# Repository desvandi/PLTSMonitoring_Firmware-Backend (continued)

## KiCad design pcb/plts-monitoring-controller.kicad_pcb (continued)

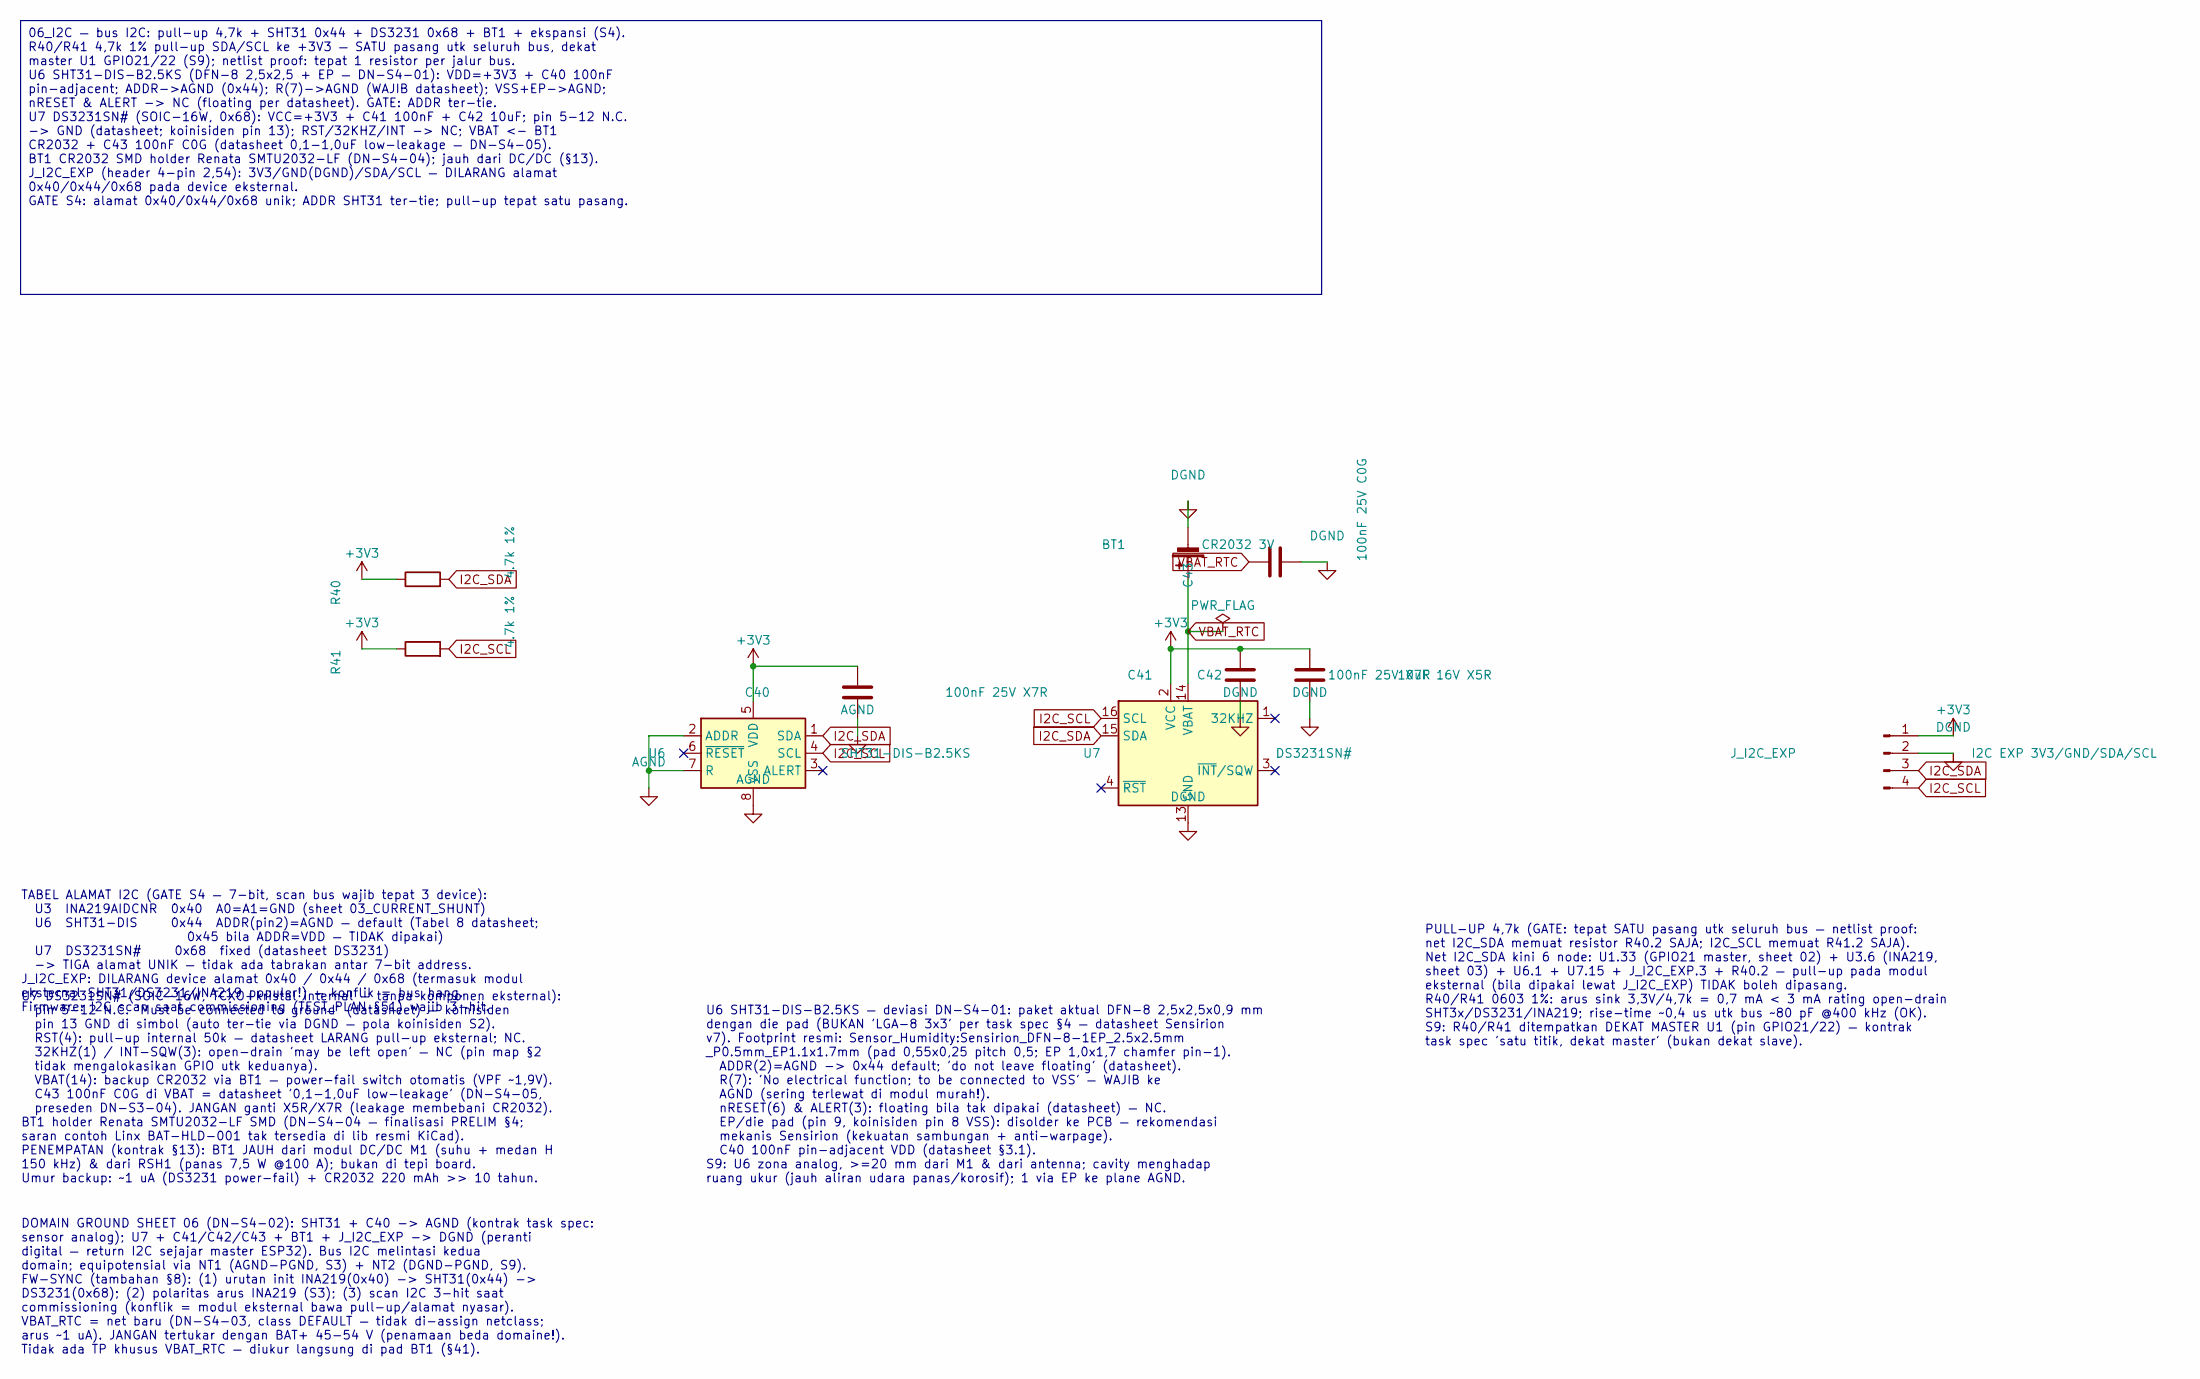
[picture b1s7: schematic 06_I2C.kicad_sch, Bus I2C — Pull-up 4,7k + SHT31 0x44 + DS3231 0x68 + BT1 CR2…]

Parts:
BT1: CR2032 3V; BatteryHolder_Renata_SMTU2032-LF_1x2032
C40, C41: 100nF 25V X7R; C_0603_1608Metric
C42: 10uF 16V X5R; C_0805_2012Metric
C43: 100nF 25V C0G; C_0603_1608Metric
J_I2C_EXP: I2C EXP 3V3/GND/SDA/SCL; PinHeader_1x04_P2.54mm_Vertical
R40, R41: 4.7k 1%; R_0603_1608Metric
U6: SHT31-DIS-B2.5KS; Sensirion_DFN-8-1EP_2.5x2.5mm_P0.5mm_EP1.1x1.7mm
U7: DS3231SN#; SOIC-16W_7.5x10.3mm_P1.27mm

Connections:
+3V3: C40.1, C41.1, C42.1, J_I2C_EXP.1, R40.1, R41.1, U6.5 (VDD), U7.2 (VCC); also elsewhere on the board
AGND: C40.2, U6.2 (ADDR), U6.7 (R), U6.8 (VSS), U6.9 (VSS); also elsewhere on the board
DGND: BT1.2 (-), C41.2, C42.2, C43.2, J_I2C_EXP.2, U7.5 (GND), U7.6 (GND), U7.7 (GND), U7.8 (GND), U7.9 (GND), U7.10 (GND), U7.11 (GND), U7.12 (GND), U7.13 (GND); also elsewhere on the board
I2C_SCL: J_I2C_EXP.4, R41.2, U6.4 (SCL), U7.16 (SCL); also elsewhere on the board
I2C_SDA: J_I2C_EXP.3, R40.2, U6.1 (SDA), U7.15 (SDA); also elsewhere on the board
VBAT_RTC: BT1.1 (+), C43.1, U7.14 (VBAT)

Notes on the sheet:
TABEL ALAMAT I2C (GATE S4 — 7-bit, scan bus wajib tepat 3 device): U3 INA219AIDCNR 0x40 A0=A1=GND (sheet 03_CURRENT_SHUNT) U6 SHT31-DIS 0x44 ADDR(pin2)=AGND — default (Tabel 8 datasheet; 0x45 bila ADDR=VDD — TIDAK dipakai) U7 DS3231SN# 0x68 fixed (datasheet DS3231) -> TIGA alamat UNIK — tidak ada t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
PULL-UP 4,7k (GATE: tepat SATU pasang utk seluruh bus — netlist proof: net I2C_SDA memuat resistor R40.2 SAJA; I2C_SCL memuat R41.2 SAJA). Net I2C_SDA kini 6 node: U1.33 (GPIO21 master, sheet 02) + U3.6 (INA219, sheet 03) + U6.1 + U7.15 + J_I2C_EXP.3 + R40.2 — pull-up pada modul eksternal (bila dip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
U7 DS3231SN# (SOIC-16W, TCXO+kristal internal — tanpa komponen eksternal): pin 5-12 N.C. 'Must be connected to ground' (datasheet) — koinisiden pin 13 GND di simbol (auto ter-tie via DGND — pola koinisiden S2). RST(4): pull-up internal 50k — datasheet LARANG pull-up eksternal; NC. 32KHZ(1) / INT-SQ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
U6 SHT31-DIS-B2.5KS — deviasi DN-S4-01: paket aktual DFN-8 2,5x2,5x0,9 mm dengan die pad (BUKAN 'LGA-8 3x3' per task spec §4 — datasheet Sensirion v7). Footprint resmi: Sensor_Humidity:Sensirion_DFN-8-1EP_2.5x2.5mm _P0.5mm_EP1.1x1.7mm (pad 0,55x0,25 pitch 0,5; EP 1,0x1,7 chamfer pin-1). ADDR(2)=AGN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
DOMAIN GROUND SHEET 06 (DN-S4-02): SHT31 + C40 -> AGND (kontrak task spec: sensor analog); U7 + C41/C42/C43 + BT1 + J_I2C_EXP -> DGND (peranti digital — return I2C sejajar master ESP32). Bus I2C melintasi kedua domain; equipotensial via NT1 (AGND-PGND, S3) + NT2 (DGND-PGND, S9). FW-SYNC (tambahan §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
06_I2C — bus I2C: pull-up 4,7k + SHT31 0x44 + DS3231 0x68 + BT1 + ekspansi (S4). R40/R41 4,7k 1% pull-up SDA/SCL ke +3V3 — SATU pasang utk seluruh bus, dekat master U1 GPIO21/22 (S9); netlist proof: tepat 1 resistor per jalur bus. U6 SHT31-DIS-B2.5KS (DFN-8 2,5x2,5 + EP — DN-S4-01): VDD=+3V3 + C40 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

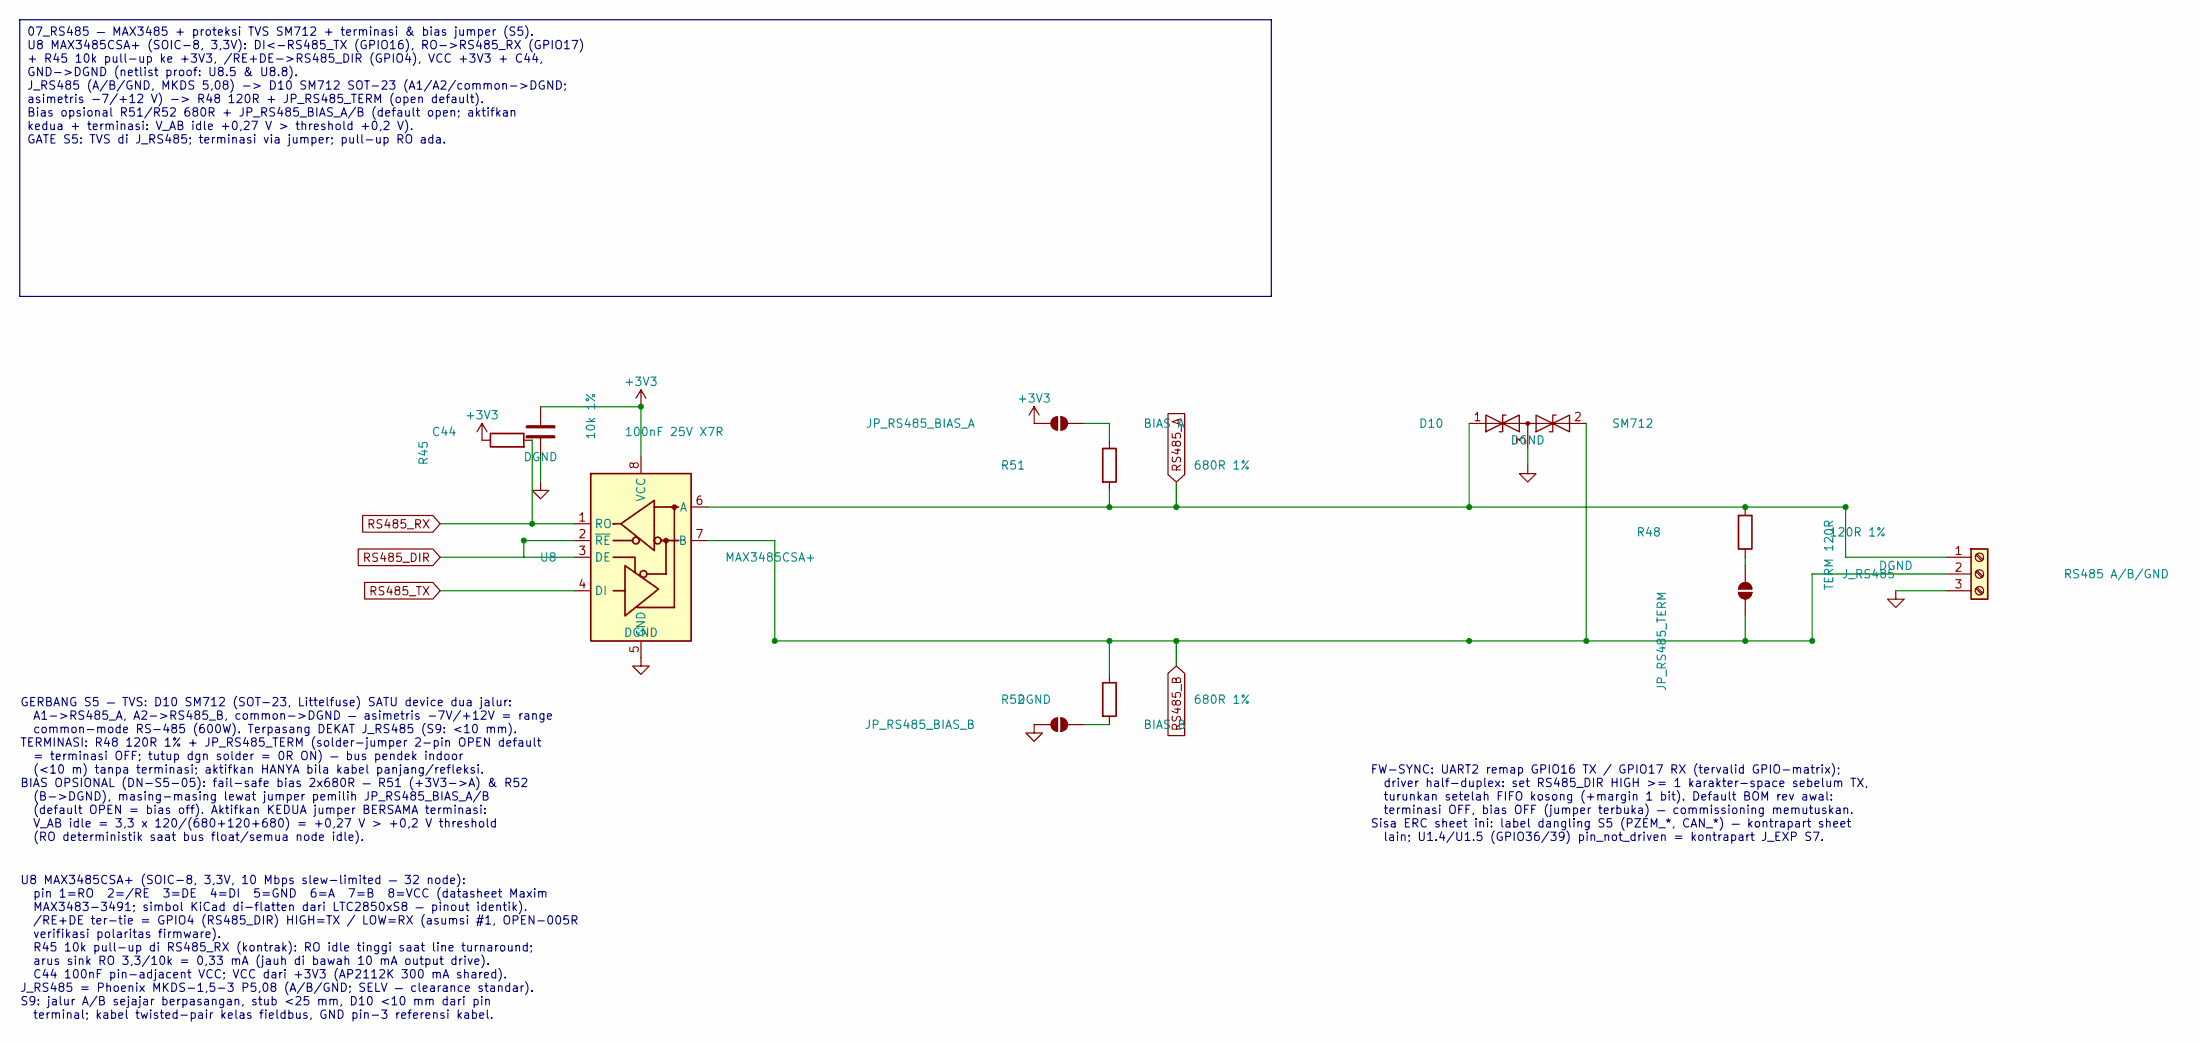
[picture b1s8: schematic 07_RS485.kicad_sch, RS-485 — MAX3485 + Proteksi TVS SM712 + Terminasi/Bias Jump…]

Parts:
C44: 100nF 25V X7R; C_0603_1608Metric
D10: SM712; SOT-23
JP_RS485_BIAS_A: BIAS A; SolderJumper-2_P1.3mm_Open_Pad1.0x1.5mm
JP_RS485_BIAS_B: BIAS B; SolderJumper-2_P1.3mm_Open_Pad1.0x1.5mm
JP_RS485_TERM: TERM 120R; SolderJumper-2_P1.3mm_Open_Pad1.0x1.5mm
J_RS485: RS485 A/B/GND; TerminalBlock_Phoenix_MKDS-1,5-3-5.08_1x03_P5.08mm_Horizont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
R45: 10k 1%; R_0603_1608Metric
R48: 120R 1%; R_0603_1608Metric
R51, R52: 680R 1%; R_0603_1608Metric
U8: MAX3485CSA+; SOIC-8_3.9x4.9mm_P1.27mm

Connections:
+3V3: C44.1, JP_RS485_BIAS_A.1 (A), R45.1, U8.8 (VCC); also elsewhere on the board
DGND: C44.2, D10.3 (common), JP_RS485_BIAS_B.1 (A), J_RS485.3, U8.5 (GND); also elsewhere on the board
unnamed: JP_RS485_BIAS_A.2 (B), R51.1
unnamed: JP_RS485_BIAS_B.2 (B), R52.2
unnamed: JP_RS485_TERM.2 (B), R48.2
RS485_A: D10.1 (A1), J_RS485.1, R48.1, R51.2, U8.6 (A); also elsewhere on the board
RS485_B: D10.2 (A2), JP_RS485_TERM.1 (A), J_RS485.2, R52.1, U8.7 (B); also elsewhere on the board
RS485_DIR: U8.2 (~RE), U8.3 (DE); also elsewhere on the board
RS485_RX: R45.2, U8.1 (RO); also elsewhere on the board
RS485_TX: U8.4 (DI); also elsewhere on the board

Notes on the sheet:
GERBANG S5 — TVS: D10 SM712 (SOT-23, Littelfuse) SATU device dua jalur: A1->RS485_A, A2->RS485_B, common->DGND — asimetris -7V/+12V = range common-mode RS-485 (600W). Terpasang DEKAT J_RS485 (S9: <10 mm). TERMINASI: R48 120R 1% + JP_RS485_TERM (solder-jumper 2-pin OPEN default = terminasi OFF; tutu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
U8 MAX3485CSA+ (SOIC-8, 3,3V, 10 Mbps slew-limited — 32 node): pin 1=RO 2=/RE 3=DE 4=DI 5=GND 6=A 7=B 8=VCC (datasheet Maxim MAX3483-3491; simbol KiCad di-flatten dari LTC2850xS8 — pinout identik). /RE+DE ter-tie = GPIO4 (RS485_DIR) HIGH=TX / LOW=RX (asumsi #1, OPEN-005R verifikasi polaritas firmwa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
FW-SYNC: UART2 remap GPIO16 TX / GPIO17 RX (tervalid GPIO-matrix); driver half-duplex: set RS485_DIR HIGH >= 1 karakter-space sebelum TX, turunkan setelah FIFO kosong (+margin 1 bit). Default BOM rev awal: terminasi OFF, bias OFF (jumper terbuka) — commissioning memutuskan. Sisa ERC sheet ini: labe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
07_RS485 — MAX3485 + proteksi TVS SM712 + terminasi & bias jumper (S5). U8 MAX3485CSA+ (SOIC-8, 3,3V): DI<-RS485_TX (GPIO16), RO->RS485_RX (GPIO17) + R45 10k pull-up ke +3V3, /RE+DE->RS485_DIR (GPIO4), VCC +3V3 + C44, GND->DGND (netlist proof: U8.5 & U8.8). J_RS485 (A/B/GND, MKDS 5,08) -> D10 SM712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

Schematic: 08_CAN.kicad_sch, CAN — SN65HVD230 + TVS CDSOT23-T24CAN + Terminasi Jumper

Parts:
C70: 100nF 25V X7R; C_0603_1608Metric
D20: CDSOT23-T24CAN; SOT-23
JP_CAN_TERM: TERM 120R; SolderJumper-2_P1.3mm_Open_Pad1.0x1.5mm
J_CAN: CAN CANH/CANL/GND; TerminalBlock_Phoenix_MKDS-1,5-3-5.08_1x03_P5.08mm_Horizont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
R49: 120R 1%; R_0603_1608Metric
U9: SN65HVD230DR; SOIC-8_3.9x4.9mm_P1.27mm

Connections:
+3V3: C70.1, U9.3 (VCC); also elsewhere on the board
CAN_H: D20.1 (CANH), J_CAN.1, R49.1, U9.7 (CANH); also elsewhere on the board
CAN_L: D20.2 (CANL), JP_CAN_TERM.1 (A), J_CAN.2, U9.6 (CANL); also elsewhere on the board
CAN_RX: U9.4 (R); also elsewhere on the board
CAN_TX: U9.1 (D); also elsewhere on the board
DGND: C70.2, D20.3 (GND), J_CAN.3, U9.2 (GND), U9.8 (Rs); also elsewhere on the board
unnamed: JP_CAN_TERM.2 (B), R49.2

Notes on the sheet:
GERBANG S5 — TVS: D20 CDSOT23-T24CAN (Bourns, SOT-23): 1=CANH, 2=CANL, 3=GND — array CAN-rated VRWM 24V (clamping ~40V; aman thd dominant 3,5V/ recessive 2,5V bus 5V + common-mode). TIDAK ada di lib resmi 9.0.2 -> simbol custom plts-custom:TVS_CAN diturunkan programatik dari SM712_SOT23 (topologi p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
U9 SN65HVD230DR (SOIC-8, 3,3V, TI): 1=TXD 2=GND 3=VCC 4=RXD 5=VREF 6=CANL 7=CANH 8=RS. TXD<-CAN_TX (GPIO25, TWAI TX), RXD->CAN_RX (GPIO26). C70 100nF pin-adjacent. Standby/low-power TIDAK dipakai. ESP32 TWAI driver terintegrasi (bit timing 500 kbps — konfig FW). J_CAN = Phoenix MKDS-1,5-3 P5,08 (CA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
FW-SYNC: TWAI (CAN) ESP32 di GPIO25/26 — pin matrix remap valid; dua node PLTS + inverter hybrid: bitrate 500 kbps standar PLTS. Driver SJA1000-compat; filter HW utk ID telemetri. Catatan ERC: VREF NC (output tanpa beban — bukan pelanggaran); label CAN_TX/CAN_RX kontrapart sheet 02 (U1 GPIO25/26).
08_CAN — SN65HVD230 + TVS CDSOT23-T24CAN + terminasi jumper (S5). U9 SN65HVD230DR (SOIC-8, 3,3V): TXD<-CAN_TX (GPIO25), RXD->CAN_RX (GPIO26), RS->DGND LANGSUNG (high-speed — kontrak; netlabel CAN_RS tak terpakai), VCC +3V3 + C70 100nF, GND->DGND, VREF->NC. J_CAN (CANH/CANL/GND, MKDS 5,08) -> D20 CD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

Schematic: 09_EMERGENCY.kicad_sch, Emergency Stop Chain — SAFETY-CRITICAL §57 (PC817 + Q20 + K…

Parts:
C75: 100nF 25V X7R; C_0603_1608Metric
D21: SS14 40V/1A; D_SMA
D22, D23: SMAJ5.0A; D_SMA
J_ESTOP: E-STOP LOOP NC; TerminalBlock_Phoenix_MKDS-1,5-2-5.08_1x02_P5.08mm_Horizont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
J_RELAY: RELAY COM/NO DRY; TerminalBlock_Phoenix_MKDS-1,5-2-5.08_1x02_P5.08mm_Horizont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
K1: HF115F-1/5V-H; Relay_HF115F_1
OPT1: PC817; DIP-4_W7.62mm
Q20: AO3400A; SOT-23
Q21: BSS138; SOT-23
R70: 100R 1%; R_0603_1608Metric
R71, R77: 100k 1%; R_0603_1608Metric
R72: 330R 1%; R_0603_1608Metric
R75: 47k 1%; R_0603_1608Metric
R76, R78: 10k 1%; R_0603_1608Metric

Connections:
+3V3: R72.1, R76.2, R78.2; also elsewhere on the board
+5V: OPT1.4; also elsewhere on the board
+5V_RELAY: D22.2 (A2), J_ESTOP.1; also elsewhere on the board
DGND: C75.2, Q21.2 (S), R77.2; also elsewhere on the board
E_STOP_SENSE: C75.1, Q21.3 (D), R76.1; also elsewhere on the board
unnamed: D21.2 (A), K1.2 (COIL-), Q20.3 (D)
unnamed: J_RELAY.1, K1.3 (COM)
unnamed: J_RELAY.2, K1.4 (NO)
unnamed: OPT1.1, R72.2
unnamed: OPT1.3, R70.1
unnamed: Q20.1 (G), R70.2, R71.1
unnamed: Q21.1 (G), R75.2, R77.1
PGND: D22.1 (A1), D23.1 (A1), Q20.2 (S), R71.2; also elsewhere on the board
RELAY_CTRL: OPT1.2, R78.1; also elsewhere on the board
RELAY_RET: D21.1 (K), D23.2 (A2), J_ESTOP.2, K1.1 (COIL+), R75.1; also elsewhere on the board

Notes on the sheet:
TABEL KEBENARAN §57 — SEMUA KONDISI GAGAL → K1 DE-ENERGIZED (SAFETY REVIEW): 1. ESP32 OFF / reset / boot / crash / watchdog → GPIO27 floating → R78 pull-up +3V3 → LED PC817 MATI → Q20 OFF (R71) → K1 OFF (fail-safe) 2. GPIO27 stuck-HIGH (fault MCU) → LED mati (aktif-LOW!) → Q20 OFF → K1 OFF 3. Rail 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
TOPOLOGI R1+R2 (FIX 2026-09-05) — KONTRAK FIRMWARE AKTIF-LOW: E-STOP MEMUTUS SISI SUPPLAI COIL — BUKAN SISI DRAIN — TIDAK DIUBAH. GPIO27 = AKTIF-LOW (kontrak EmergencyRelayDriver repo): +3V3 → R72 330R → anoda PC817; katoda → RELAY_CTRL (IO27 SINK, (3,3−1,2)/330 = 6,4 mA; IF maks PC817 50 mA). R78 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
KOMPONEN KUNCI + ITEM VERIFIKASI BOM (GATE e SAFETY REVIEW): OPT1 PC817 (DIP-4; Vce 80 V, CTR 50–300%): isolasi drive — LED: anoda dari +3V3 via R72 (domain ESP32), katoda ke RELAY_CTRL (IO27 SINK 6,4 mA — dalam rating GPIO ESP32); output C=+5V, E=R70 (DN-S6-02). Q20 AO3400A (SOT-23; 30 V/5,7 A; Vg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
PENEMPATAN (S9): rantai E-stop di zona power dekat tepi board; loop J_ESTOP pendek & jauh dari antenna ESP32; K1 kontak menjauh dari zona analog; jalur PGND source Q20 langsung ke star; D21 dekat pin coil K1; D22/D23 < 10 mm dari J_ESTOP; cluster sense Q21/R75/R76/R77/C75 dekat TP_ESTOP (sheet 11) 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
09_EMERGENCY — rantai E-stop SAFETY-CRITICAL (rev R1+R2, §57/§11.1). Drive AKTIF-LOW (R1 — kontrak firmware): +3V3 → R72 330R → OPT1 PC817 anoda; KATODA → RELAY_CTRL = GPIO27 (IO27 SINK 6,4 mA; LOW = ON); R78 10k pull-up +3V3 → boot/reset/floating = LED OFF = K1 OFF. Output opto: C=+5V → R70 100R →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

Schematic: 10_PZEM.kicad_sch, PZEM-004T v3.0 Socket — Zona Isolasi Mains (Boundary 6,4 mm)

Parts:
D30: BAV199; SOT-23
F3: 1A T 250VAC 5x20; Fuseholder_Clip-5x20mm_Littelfuse_111_Inline_P20.00x5.00mm_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
J_PZEM_AC: MAINS L/N 250VAC; TerminalBlock_Dinkle_DT-55-B01X-02_P10.00mm
M_PZEM: PZEM-004T v3.0 100A-CT; Module_PZEM_004T_Socket; not fitted
R55: 1k 1%; R_0603_1608Metric
RV3: MOV 275VAC DNP; RV_Disc_D21.5mm_W5mm_P10mm; not fitted

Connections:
+3V3: D30.2 (A); also elsewhere on the board
+5V: M_PZEM.3 (5V); also elsewhere on the board
DGND: D30.1 (K), M_PZEM.4 (GND); also elsewhere on the board
L_AC: F3.1, J_PZEM_AC.1
L_AC_FUSED: F3.2, M_PZEM.1 (L), RV3.1
N_AC: J_PZEM_AC.2, M_PZEM.2 (N), RV3.2
unnamed: M_PZEM.5 (TX), R55.1
PZEM_RX: D30.3 (K), R55.2; also elsewhere on the board
PZEM_TX: M_PZEM.6 (RX); also elsewhere on the board

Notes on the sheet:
ZONA MAINS TERISOLASI (audit §11.3 / keputusan D5): net L_AC, N_AC, L_AC_FUSED (DN-S5-04) = class MAINS_AC — DRC custom MAINS_SELV_CREEPAGE (clearance >= 6,4 mm ke SEMUA net non-MAINS_AC) + MAINS_LN_SPACING (L-N >= 6,4 mm) — rule .kicad_dru sejak S0. Lebar 0,5 mm cukup (arus sampling mA — CT ekster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
M_PZEM socket modul PZEM-004T v3.0 100A-CT (DNP rev awal — DN-S5-07): L/N (kiri, MAINS) <- L_AC_FUSED/N_AC via wiring harness socket; TTL (kanan, SELV): 5V<-+5V (~25 mA), GND->DGND, TX->R55 1k -> PZEM_RX (GPIO18), RX<-PZEM_TX (GPIO19). Modul terisolasi opto internal (audit §11.3: sisi TTL murni SEL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
PENEMPATAN (S9): seluruh zona mains di tepi board terpisah; J_PZEM_AC + F3 + RV3 + pad L/N M_PZEM dalam satu region; TIDAK ada net SELV melintasi region; routing MAINS satu layer (top), jauh dari antenna & analog. ENCLOSURE: akses servis F3 dari luar (fuse dapat diganti tanpa membuka zona lain); la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
10_PZEM — socket PZEM-004T v3.0 di zona isolasi mains (S5). J_PZEM_AC (L_AC/N_AC, Dinkle DT-55 P10 — DN-S5-06) + F3 1A slow 250VAC di jalur L + RV3 MOV 275VAC DNP -> net L_AC/N_AC/L_AC_FUSED class MAINS_AC (DN-S5-04; clearance 6,4 mm DRC custom + slot milled S9). M_PZEM (DNP, custom plts-custom:M_P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

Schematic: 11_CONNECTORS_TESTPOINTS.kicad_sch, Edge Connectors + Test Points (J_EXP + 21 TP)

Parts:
J_EXP: EXPANSION 7-PIN 2,54; PinHeader_1x07_P2.54mm_Vertical
TP_3V3: +3V3; TestPoint_Pad_D2.0mm
TP_5V: +5V; TestPoint_Pad_D2.0mm
TP_5V_RELAY: +5V_RELAY; TestPoint_Pad_D2.0mm
TP_ACS1_ADC: ACS1_ADC; TestPoint_Pad_D2.0mm
TP_ACS2_ADC: ACS2_ADC; TestPoint_Pad_D2.0mm
TP_BAT+: BAT+; TestPoint_Pad_D2.0mm
TP_CAN_H: CAN_H; TestPoint_Pad_D2.0mm
TP_CAN_L: CAN_L; TestPoint_Pad_D2.0mm
TP_EN: EN; TestPoint_Pad_D2.0mm
TP_ESTOP: E_STOP_SENSE; TestPoint_Pad_D2.0mm
TP_GND: PGND; TestPoint_Pad_D2.0mm
TP_IO0: IO0; TestPoint_Pad_D2.0mm
TP_RELAY_CTRL: RELAY_CTRL; TestPoint_Pad_D2.0mm
TP_RELAY_RET: RELAY_RET; TestPoint_Pad_D2.0mm
TP_RS485_A: RS485_A; TestPoint_Pad_D2.0mm
TP_RS485_B: RS485_B; TestPoint_Pad_D2.0mm
TP_SHUNT_K+: SHUNT_K+; TestPoint_Pad_D2.0mm
TP_SHUNT_K-: SHUNT_K-; TestPoint_Pad_D2.0mm
TP_UART_RX: UART0_RX; TestPoint_Pad_D2.0mm
TP_UART_TX: UART0_TX; TestPoint_Pad_D2.0mm
TP_VBAT: VBAT_DIV; TestPoint_Pad_D2.0mm

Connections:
+3V3: J_EXP.1, TP_3V3.1; also elsewhere on the board
+5V: TP_5V.1; also elsewhere on the board
+5V_RELAY: TP_5V_RELAY.1; also elsewhere on the board
ACS1_ADC: TP_ACS1_ADC.1; also elsewhere on the board
ACS2_ADC: TP_ACS2_ADC.1; also elsewhere on the board
BAT+: TP_BAT+.1; also elsewhere on the board
CAN_H: TP_CAN_H.1; also elsewhere on the board
CAN_L: TP_CAN_L.1; also elsewhere on the board
DGND: J_EXP.2; also elsewhere on the board
EN: TP_EN.1; also elsewhere on the board
E_STOP_SENSE: TP_ESTOP.1; also elsewhere on the board
GPIO13: J_EXP.3; also elsewhere on the board
GPIO23: J_EXP.4; also elsewhere on the board
GPIO33: J_EXP.5; also elsewhere on the board
GPIO36: J_EXP.6; also elsewhere on the board
GPIO39: J_EXP.7; also elsewhere on the board
IO0: TP_IO0.1; also elsewhere on the board
PGND: TP_GND.1; also elsewhere on the board
RELAY_CTRL: TP_RELAY_CTRL.1; also elsewhere on the board
RELAY_RET: TP_RELAY_RET.1; also elsewhere on the board
RS485_A: TP_RS485_A.1; also elsewhere on the board
RS485_B: TP_RS485_B.1; also elsewhere on the board
SHUNT_K+: TP_SHUNT_K+.1; also elsewhere on the board
SHUNT_K-: TP_SHUNT_K-.1; also elsewhere on the board
UART0_RX: TP_UART_RX.1; also elsewhere on the board
UART0_TX: TP_UART_TX.1; also elsewhere on the board
VBAT_DIV: TP_VBAT.1; also elsewhere on the board

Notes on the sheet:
J_EXP — HEADER EKSPANSI 7-PIN 2,54 (M5 audit): 1=3V3 · 2=GND (DGND, zona digital — konsisten J_PROGRAM/J_I2C_EXP) · 3=GPIO13 · 4=GPIO23 · 5=GPIO33 (ADC1, bidirectional) · 6=GPIO36/SENSOR_VP · 7=GPIO39/ SENSOR_VN. GPIO36 & GPIO39 = INPUT-ONLY (ADC1) — firmware DILARANG drive-out; semua kanal ADC eks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
TEST POINT — POWER (5/21)
TEST POINT — ANALOG (5/21)
TEST POINT — KONTROL/SAFETY (5/21)
TEST POINT — KOMUNIKASI (6/21)
KONVENSI & PENEMPATAN TP (layout S9): Pad bulat SMD D2,0 mm bare-copper (TestPoint_Pad_D2.0mm — DN-S7-05); pitch antar-TP >= 2,54 mm; TIDAK di bawah komponen / modul M1 / RSH1; tersebar per zona mengikuti sheet asal netnya. TP_GND = PGND star (BATTERY-) — referensi umum DMM (DN-S7-02; AGND/ DGND eq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
INVENTARIS CONNECTOR TEPI §40 + M5 (1/2) — SEMUA hadir (netlist proof): J_BAT — 2-pin 5,08 (BAT+/BAT-) — sheet 01 — feed suplai elektronik ~65 mA J_SHUNT — 2 pad baut M5 DALAM footprint RSH1 (BATTERY- star / SYS- 100 A) — 03 J_ACS1 — 2-pin >= 30 A (ACS1 IP+/IP-) — 05 — jalur force pour dua sisi J_A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
INVENTARIS (2/2) + CATATAN M5: J_PROGRAM — header 6-pin 2,54 (3V3/GND/TX/RX/EN/IO0) — 02 J_EXP — header 7-pin 2,54 (3V3/GND/GPIO13/23/33/36/39) — 11 (sheet ini) J_I2C_EXP — header 4-pin 2,54 (3V3/GND/SDA/SCL) — 06 J1 — USB-C 16-pin (VBUS_5V/DP/DM + CC 5,1k) — 02 — VBUS TIDAK = +5V J_RS485 — 3-pin 5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
CHECKLIST GATE S7 — §40 + §41 + M5 (target 100% hijau): §40/M5 CONNECTOR (13/13 hadir — netlist proof): J_BAT(01) · J1 USB-C(02) · J_PROGRAM(02) · J_SHUNT = pad baut M5 dalam RSH1(03) · J_ACS1(05) · J_ACS2(05) · J_I2C_EXP(06) · J_RS485(07) · J_CAN(08) · J_ESTOP(09) · J_RELAY(09) · J_PZEM_AC(10) · J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
11_CONNECTORS_TESTPOINTS — inventaris connector tepi §40 + 21 test point §41 + audit M5 (S7). KOMPONEN BARU: J_EXP header 7-pin 2,54 (3V3/GND/GPIO13/23/33/36/39 — M5 audit; kontrapart 5 label dangling terakhir GPIO13/23/33/36/39 -> ERC 0 error, 0 dangling — S8-ready) + 21 TP pad bulat SMD D2,0 mm (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

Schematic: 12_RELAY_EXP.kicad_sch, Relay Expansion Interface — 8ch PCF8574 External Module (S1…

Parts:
D24, D25: SMAJ5.0A; D_SMA; not fitted
F4: 1.1A hold; Fuse_1812_4532Metric
FB2: 600R@100MHz; L_0805_2012Metric
J_RELAY_EXP: RELAY EXP 5V/GND/SDA/SCL/INT; PinHeader_2x03_P2.54mm_Vertical
Q22, Q23: BSS138; SOT-23
R79, R84: 4.7k 1%; R_0603_1608Metric
R82: 10k 1%; R_0603_1608Metric
R83: 15k 1%; R_0603_1608Metric

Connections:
+3V3: Q22.1 (G), Q23.1 (G); also elsewhere on the board
+5V: F4.1; also elsewhere on the board
+5V_RELAY_EXP: FB2.2, J_RELAY_EXP.1, R79.1, R84.1
/12_RELAY_EXP/RELAY_EXP_INT: R82.2, R83.1
I2C_SCL: Q23.2 (S); also elsewhere on the board
I2C_SDA: Q22.2 (S); also elsewhere on the board
unnamed: D24.2 (A2), J_RELAY_EXP.3, Q22.3 (D), R79.2
unnamed: D25.2 (A2), J_RELAY_EXP.5, Q23.3 (D), R84.2
unnamed: F4.2, FB2.1
unnamed: J_RELAY_EXP.6, R82.1
PGND: D24.1 (A1), D25.1 (A1), J_RELAY_EXP.2, J_RELAY_EXP.4, R83.2; also elsewhere on the board

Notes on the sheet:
S12 — RELAY EXPANSION INTERFACE (8-KANAL, PCF8574 EKSTERNAL). Sumber kontrak: docs/RELAY_INTEGRATION_ARCHITECTURE.md §2.2 + docs/ RELAY_GPIO_HARDWARE_CONTRACT.md (PCF8574 0x20, aktif-LOW, boot 0xFF = semua OFF; SDA/SCL shared GPIO21/22 — TANPA GPIO baru; INT tidak dipakai v1, disiapkan untuk readba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
PINOUT J_RELAY_EXP (2x03, PinHeader_2.54 vertikal): Pin 1 = +5V_RELAY_EXP Pin 2 = PGND Pin 3 = I2C_SDA_5V Pin 4 = PGND Pin 5 = I2C_SCL_5V Pin 6 = RELAY_EXP_INT_5V GND pin ganda (2/4) mereduksi loop arus koil pada kabel ribbon. VERIFIKASI ACCEPTANCE (item TEST_PLAN S12): 1. Bus 3V3 tetap berfungsi (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
12_RELAY_EXP — antarmuka ekspansi relai 8-kanal (S12; arsitektur §2.2). +5V -> F4 1,1A -> FB2 600R -> +5V_RELAY_EXP -> J_RELAY_EXP (2x03). I2C: bus 3V3 global (SDA/SCL) -> BSS138 Q22/Q23 -> sisi 5V (R79/R84 4k7 pull-up +5V_RELAY_EXP) -> J.3/J.5. TVS D24/D25 DNP. INT J.6 -> R82/R83 0,6 -> RELAY_EXP_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

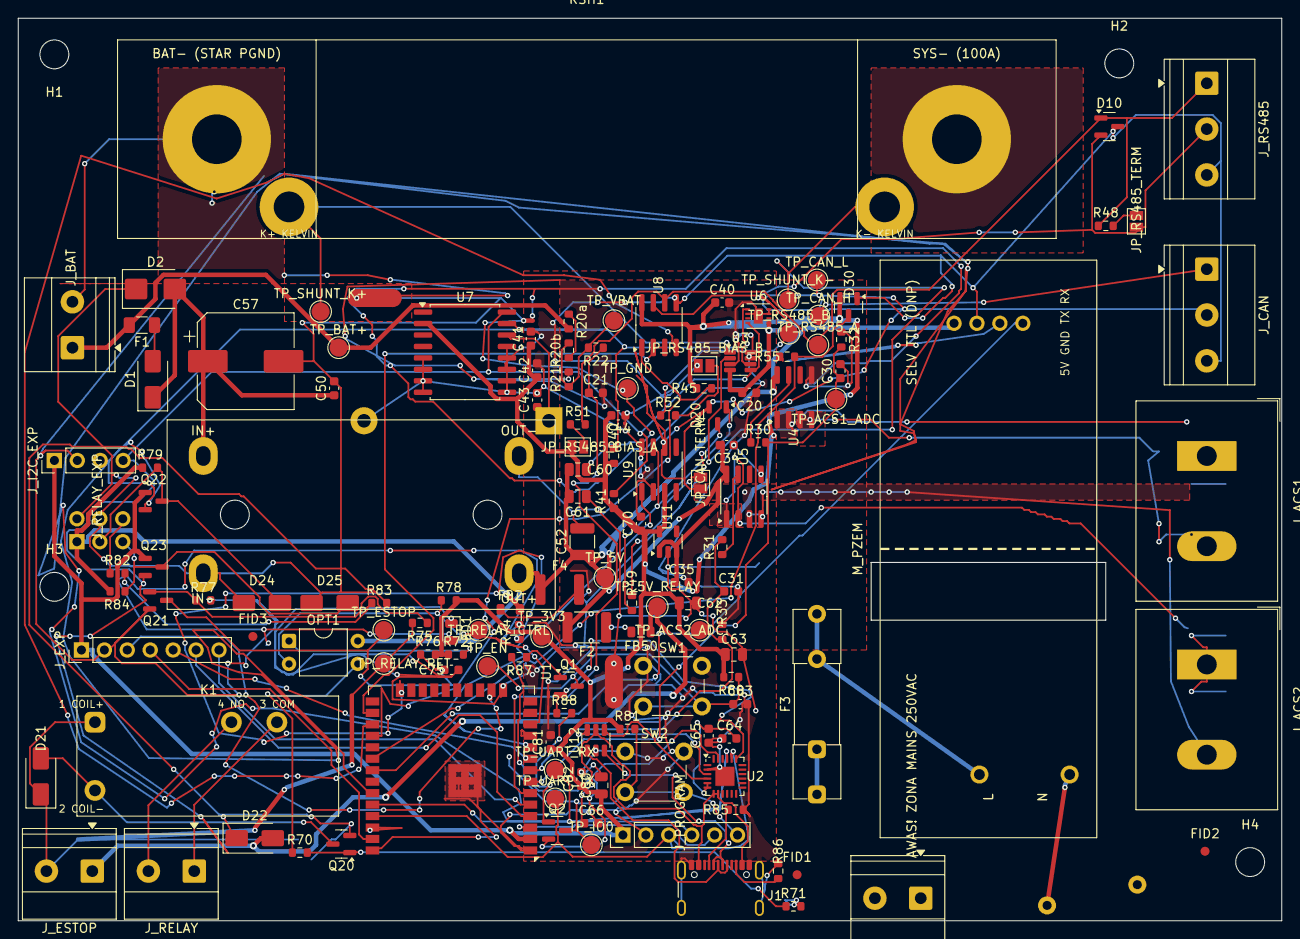
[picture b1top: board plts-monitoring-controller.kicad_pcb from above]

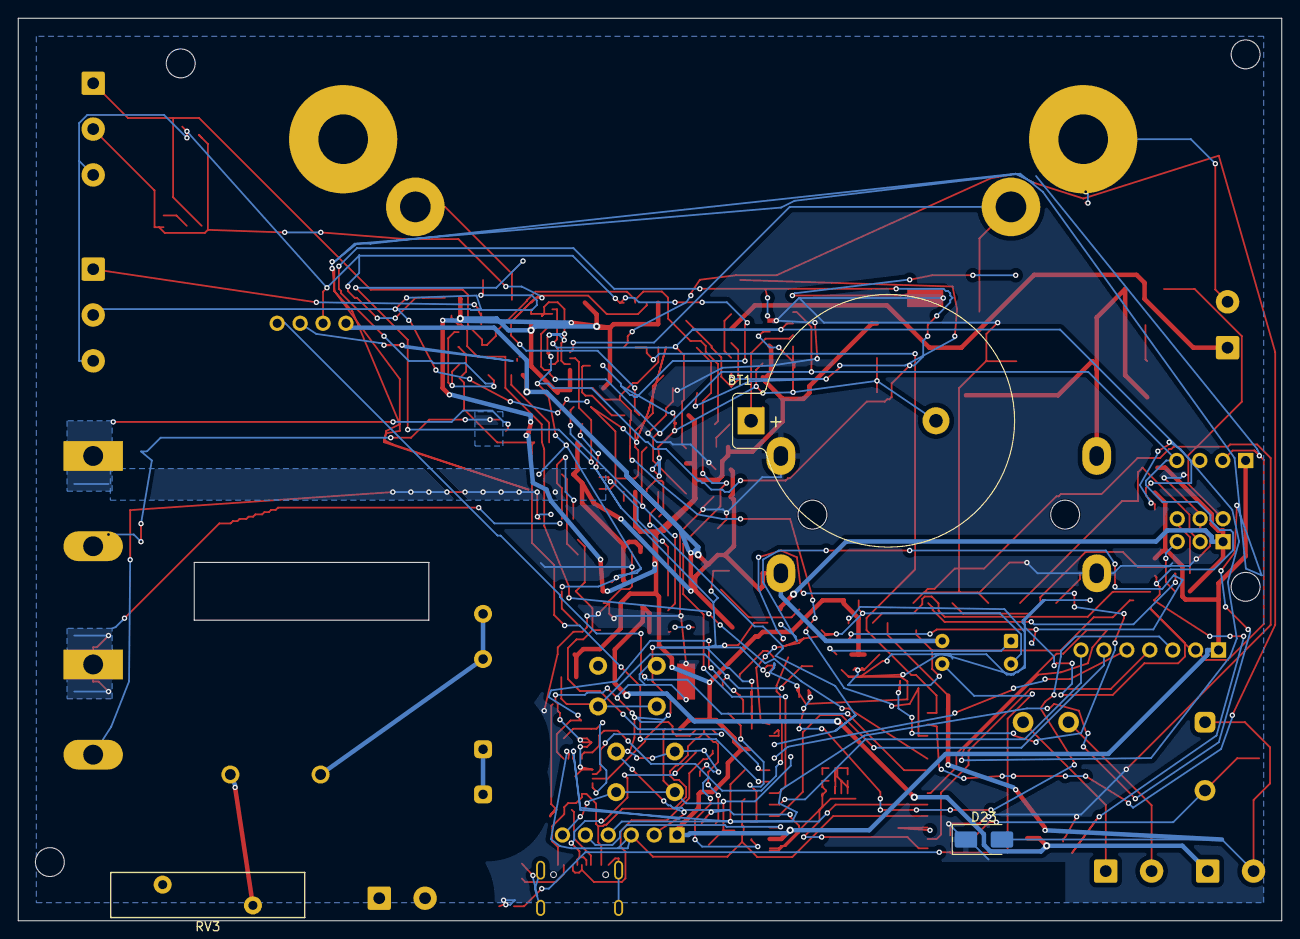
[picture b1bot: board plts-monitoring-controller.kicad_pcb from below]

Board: 2 copper layers, 140.0 x 100.0 mm, 152 parts (3 on the bottom side), 85 nets.

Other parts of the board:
FID1, FID2, FID3: Fiducial_1mm_Mask2mm
H1, H2, H3, H4: MountingHole_3.2mm_M3

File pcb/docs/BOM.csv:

Ref,Qty,Value,Footprint
R70,1,100R 1%,R_0603_1608Metric
"C20, C21, C34, C35, C40, C41, C44, C65, C66, C70, C75, C81, C82",13,100nF 25V X7R,C_0603_1608Metric
OPT1,1,PC817,DIP-4_W7.62mm
"R30, R31, R45, R78, R82",5,10k 1%,R_0603_1608Metric
"R85, R86",2,5.1k,R_0603_1608Metric
LED1,1,STATUS 0805,LED_0805_2012Metric
C43,1,100nF 25V C0G,C_0603_1608Metric
TP_VBAT,1,VBAT_DIV,TestPoint_Pad_D2.0mm
"R71, R77",2,100k 1%,R_0603_1608Metric
"FID1, FID2, FID3",3,Fiducial_1mm_Mask2mm,Fiducial_1mm_Mask2mm
U6,1,SHT31-DIS-B2.5KS,Sensirion_DFN-8-1EP_2.5x2.5mm_P0.5mm_EP1.1x1.7mm
"Q21, Q22, Q23",3,BSS138,SOT-23
U2,1,CP2102N-A02-GQFN24,HVQFN-24-1EP_4x4mm_P0.5mm_EP2.1x2.1mm
R74,1,1k,R_0603_1608Metric
"R80, R81, R87, R88",4,10k,R_0603_1608Metric
"R48, R49",2,120R 1%,R_0603_1608Metric
D10,1,SM712,SOT-23
RSH1,1,FL-2 100A/75mV,Shunt_FL2_100A
"Q1, Q2",2,S8050,SOT-23
F3,1,1A T 250VAC 5x20,Fuseholder_Clip-5x20mm_Littelfuse_111_Inline_P20.00x5.00mm_D1.05mm_Horizontal
TP_EN,1,EN,TestPoint_Pad_D2.0mm
"D22, D23, D24, D25",4,SMAJ5.0A,D_SMA
"FB2, FB50",2,600R@100MHz,L_0805_2012Metric
"JP_CAN_TERM, JP_RS485_TERM",2,TERM 120R,SolderJumper-2_P1.3mm_Open_Pad1.0x1.5mm
"H1, H2, H3, H4",4,MountingHole_3.2mm_M3,MountingHole_3.2mm_M3
C64,1,4.7uF 16V X5R,C_0603_1608Metric
Q20,1,AO3400A,SOT-23
TP_RS485_A,1,RS485_A,TestPoint_Pad_D2.0mm
"R20a, R20b",2,49.9k 1% 0805,R_0603_1608Metric
U7,1,DS3231SN#,SOIC-16W_7.5x10.3mm_P1.27mm
SW2,1,BOOT,SW_PUSH_6mm
"U4, U5",2,ACS712ELCTR-30A-T,SOIC-8_3.9x4.9mm_P1.27mm
TP_CAN_H,1,CAN_H,TestPoint_Pad_D2.0mm
R75,1,47k 1%,R_0603_1608Metric
C42,1,10uF 16V X5R,C_0603_1608Metric
TP_GND,1,PGND,TestPoint_Pad_D2.0mm
NT0,1,NET-TIE PGND-BAT- (STAR),NetTie-2_SMD_Pad2.0mm
"R32, R33, R83",3,15k 1%,R_0603_1608Metric
"R40, R41, R79, R84",4,4.7k 1%,R_0603_1608Metric
F4,1,1.1A hold,Fuse_1812_4532Metric
"C61, C63",2,100nF 50V X7R,C_0805_2012Metric
TP_UART_RX,1,UART0_RX,TestPoint_Pad_D2.0mm
R72,1,330R 1%,R_0603_1608Metric
R76,1,68k 1%,R_0603_1608Metric
TP_SHUNT_K+,1,SHUNT_K+,TestPoint_Pad_D2.0mm
TP_RS485_B,1,RS485_B,TestPoint_Pad_D2.0mm
J_EXP,1,"EXPANSION 7-PIN 2,54",PinHeader_1x07_P2.54mm_Vertical
NT1,1,NET-TIE AGND-PGND,NetTie-2_SMD_Pad0.5mm
TP_3V3,1,+3V3,TestPoint_Pad_D2.0mm
J_PROGRAM,1,PROG 3V3/GND/TX/RX/EN/IO0,PinHeader_1x06_P2.54mm_Vertical
M_PZEM,1,PZEM-004T v3.0 100A-CT,Module_PZEM_004T_Socket
TP_CAN_L,1,CAN_L,TestPoint_Pad_D2.0mm
C83,1,1uF 25V X7R,C_0603_1608Metric
TP_IO0,1,IO0,TestPoint_Pad_D2.0mm
JP_RS485_BIAS_B,1,BIAS B,SolderJumper-2_P1.3mm_Open_Pad1.0x1.5mm
J_BAT,1,BATT 45-54V,"TerminalBlock_Phoenix_MKDS-1,5-2-5.08_1x02_P5.08mm_Horizontal"
"C30, C31",2,10nF 50V X7R,C_0603_1608Metric
TP_RELAY_RET,1,RELAY_RET,TestPoint_Pad_D2.0mm
U8,1,MAX3485CSA+,SOIC-8_3.9x4.9mm_P1.27mm
TP_ACS2_ADC,1,ACS2_ADC,TestPoint_Pad_D2.0mm
J_RS485,1,RS485 A/B/GND,"TerminalBlock_Phoenix_MKDS-1,5-3-5.08_1x03_P5.08mm_Horizontal"
SW1,1,RESET,SW_PUSH_6mm
J_ESTOP,1,E-STOP LOOP NC,"TerminalBlock_Phoenix_MKDS-1,5-2-5.08_1x02_P5.08mm_Horizontal"
D2,1,SMBJ58A,D_SMB
J_RELAY,1,RELAY COM/NO DRY,"TerminalBlock_Phoenix_MKDS-1,5-2-5.08_1x02_P5.08mm_Horizontal"
TP_SHUNT_K-,1,SHUNT_K-,TestPoint_Pad_D2.0mm
U3,1,INA219AIDCNR,SOT-23-8
TP_5V,1,+5V,TestPoint_Pad_D2.0mm
TP_5V_RELAY,1,+5V_RELAY,TestPoint_Pad_D2.0mm
C52,1,47uF 25V X5R,C_1210_3225Metric
U9,1,SN65HVD230DR,SOIC-8_3.9x4.9mm_P1.27mm
"R51, R52",2,680R 1%,R_0603_1608Metric
K1,1,HF115F-1/5V-H,Relay_HF115F_1
J_RELAY_EXP,1,RELAY EXP 5V/GND/SDA/SCL/INT,PinHeader_2x03_P2.54mm_Vertical
R55,1,1k 1%,R_0603_1608Metric
"C60, C62, C80",3,10uF 16V X5R,C_0805_2012Metric
F1,1,0.5A T 63V,Fuse_1206_3216Metric
M1,1,LM2596HVS 5V,Module_LM2596HVS
F2,1,0.5A hold,Fuse_1812_4532Metric
C57,1,47uF 100V,CP_Elec_10x10.5
TP_BAT+,1,BAT+,TestPoint_Pad_D2.0mm
J_CAN,1,CAN CANH/CANL/GND,"TerminalBlock_Phoenix_MKDS-1,5-3-5.08_1x03_P5.08mm_Horizontal"
J1,1,GCT USB4105-GF-A,USB_C_Receptacle_GCT_USB4105-xx-A_16P_TopMnt_Horizontal
D30,1,BAV199,SOT-23
"J_ACS2, J_ACS1",2,DT-55-B01X-02,TerminalBlock_Dinkle_DT-55-B01X-02_P10.00mm
R21,1,5.6k 1%,R_0603_1608Metric
TP_RELAY_CTRL,1,RELAY_CTRL,TestPoint_Pad_D2.0mm
TP_ACS1_ADC,1,ACS1_ADC,TestPoint_Pad_D2.0mm
TP_ESTOP,1,E_STOP_SENSE,TestPoint_Pad_D2.0mm
R22,1,2.2k 1%,R_0603_1608Metric
U12,1,USBLC6-2SC6,SOT-23-6
D21,1,SS14 40V/1A,D_SMA
JP_RS485_BIAS_A,1,BIAS A,SolderJumper-2_P1.3mm_Open_Pad1.0x1.5mm
NT2,1,NET-TIE DGND-PGND (DIGITAL),NetTie-2_SMD_Pad2.0mm
D1,1,US1M-13-F,D_SMA
D20,1,CDSOT23-T24CAN,SOT-23
J_I2C_EXP,1,I2C EXP 3V3/GND/SDA/SCL,PinHeader_1x04_P2.54mm_Vertical
TP_UART_TX,1,UART0_TX,TestPoint_Pad_D2.0mm
C50,1,2.2uF 100V X7R,C_0603_1608Metric
J_PZEM_AC,1,MAINS L/N 250VAC,"TerminalBlock_Phoenix_MKDS-1,5-2-5.08_1x02_P5.08mm_Horizontal"
U11,1,AP2112K-3.3,SOT-23-5
U1,1,ESP32-WROOM-32E,ESP32-WROOM-32E
BT1,1,CR2032 3V,BatteryHolder_Keystone_106_1x20mm
RV3,1,MOV 275VAC DNP,RV_Disc_D21.5mm_W5mm_P10mm

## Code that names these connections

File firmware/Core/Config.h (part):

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// ---------------------------------------------------------------------------
// Canonical Hardware (brief §2)
// ---------------------------------------------------------------------------
static constexpr uint8_t  PIN_I2C_SDA       = 21;
static constexpr uint8_t  PIN_I2C_SCL       = 22;
static constexpr uint8_t  PIN_BATTERY_ADC    = 34;     // ADC1 CH6, input-only, WiFi-safe (brief §2.1)
static constexpr uint8_t  PIN_ACS712_ADC     = 35;     // ADC1 CH7, input-only
static constexpr uint32_t I2C_FREQUENCY      = 100000; // 100 kHz
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// ---------------------------------------------------------------------------
// RS485 half-duplex port (UART2 + MAX3485/MAX485 transceiver, 115200 8N1).
// Serves Modbus RTU today; the Pylontech RS485-console slot shares this port.
static constexpr uint8_t  PIN_RS485_TX       = 16;     // UART2 TX → MAX3485 DI
static constexpr uint8_t  PIN_RS485_RX       = 17;     // UART2 RX ← MAX3485 RO
static constexpr uint8_t  PIN_RS485_DE       = 4;      // DE+RE tied together (direction)
// v1.7.0 — RS485 capture-console bounds (Comm/Rs485Console.h).
static constexpr uint16_t RS485_FRAME_MAX_BYTES = 64;   // vendor console frames are short
static constexpr uint16_t RS485_FRAME_GAP_MS    = 6;    // bus-idle frame boundary
static constexpr uint8_t  RS485_FRAME_RING      = 16;   // last N frames served via REST
// CAN 2.0 port (TWAI controller + SN65HVD230 transceiver, 500 kbps).
static constexpr uint8_t  PIN_CAN_TX         = 25;     // TWAI TX → SN65HVD230 TXD
static constexpr uint8_t  PIN_CAN_RX         = 26;     // TWAI RX ← SN65HVD230 RXD

// ---------------------------------------------------------------------------
// v1.7.0 — E-WAVE emergency layer pins (parity with firmware-generic).
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// non-strapping, and NOT ADC1 — pin 32 stays reserved for a possible future
// second ACS712 (genset channel of the E-WAVE layer).
// ---------------------------------------------------------------------------
static constexpr uint8_t  PIN_PZEM_RX         = 18;     // UART1 RX <- PZEM TX
static constexpr uint8_t  PIN_PZEM_TX         = 19;     // UART1 TX -> PZEM RX
static constexpr uint32_t PZEM_BAUD           = 9600;   // PZEM-004T v3 fixed rate
static constexpr uint32_t PZEM_POLL_MS        = 1000;   // 1 Hz measurement
static constexpr uint32_t PZEM_TIMEOUT_MS     = 400;    // response window
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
